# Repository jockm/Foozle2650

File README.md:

# Foozle2650
A Signetics 2650 based SBC based on [Jim11662418's Signetics-2650-SBC](https://github.com/jim11662418/Signetics-2650-SBC)

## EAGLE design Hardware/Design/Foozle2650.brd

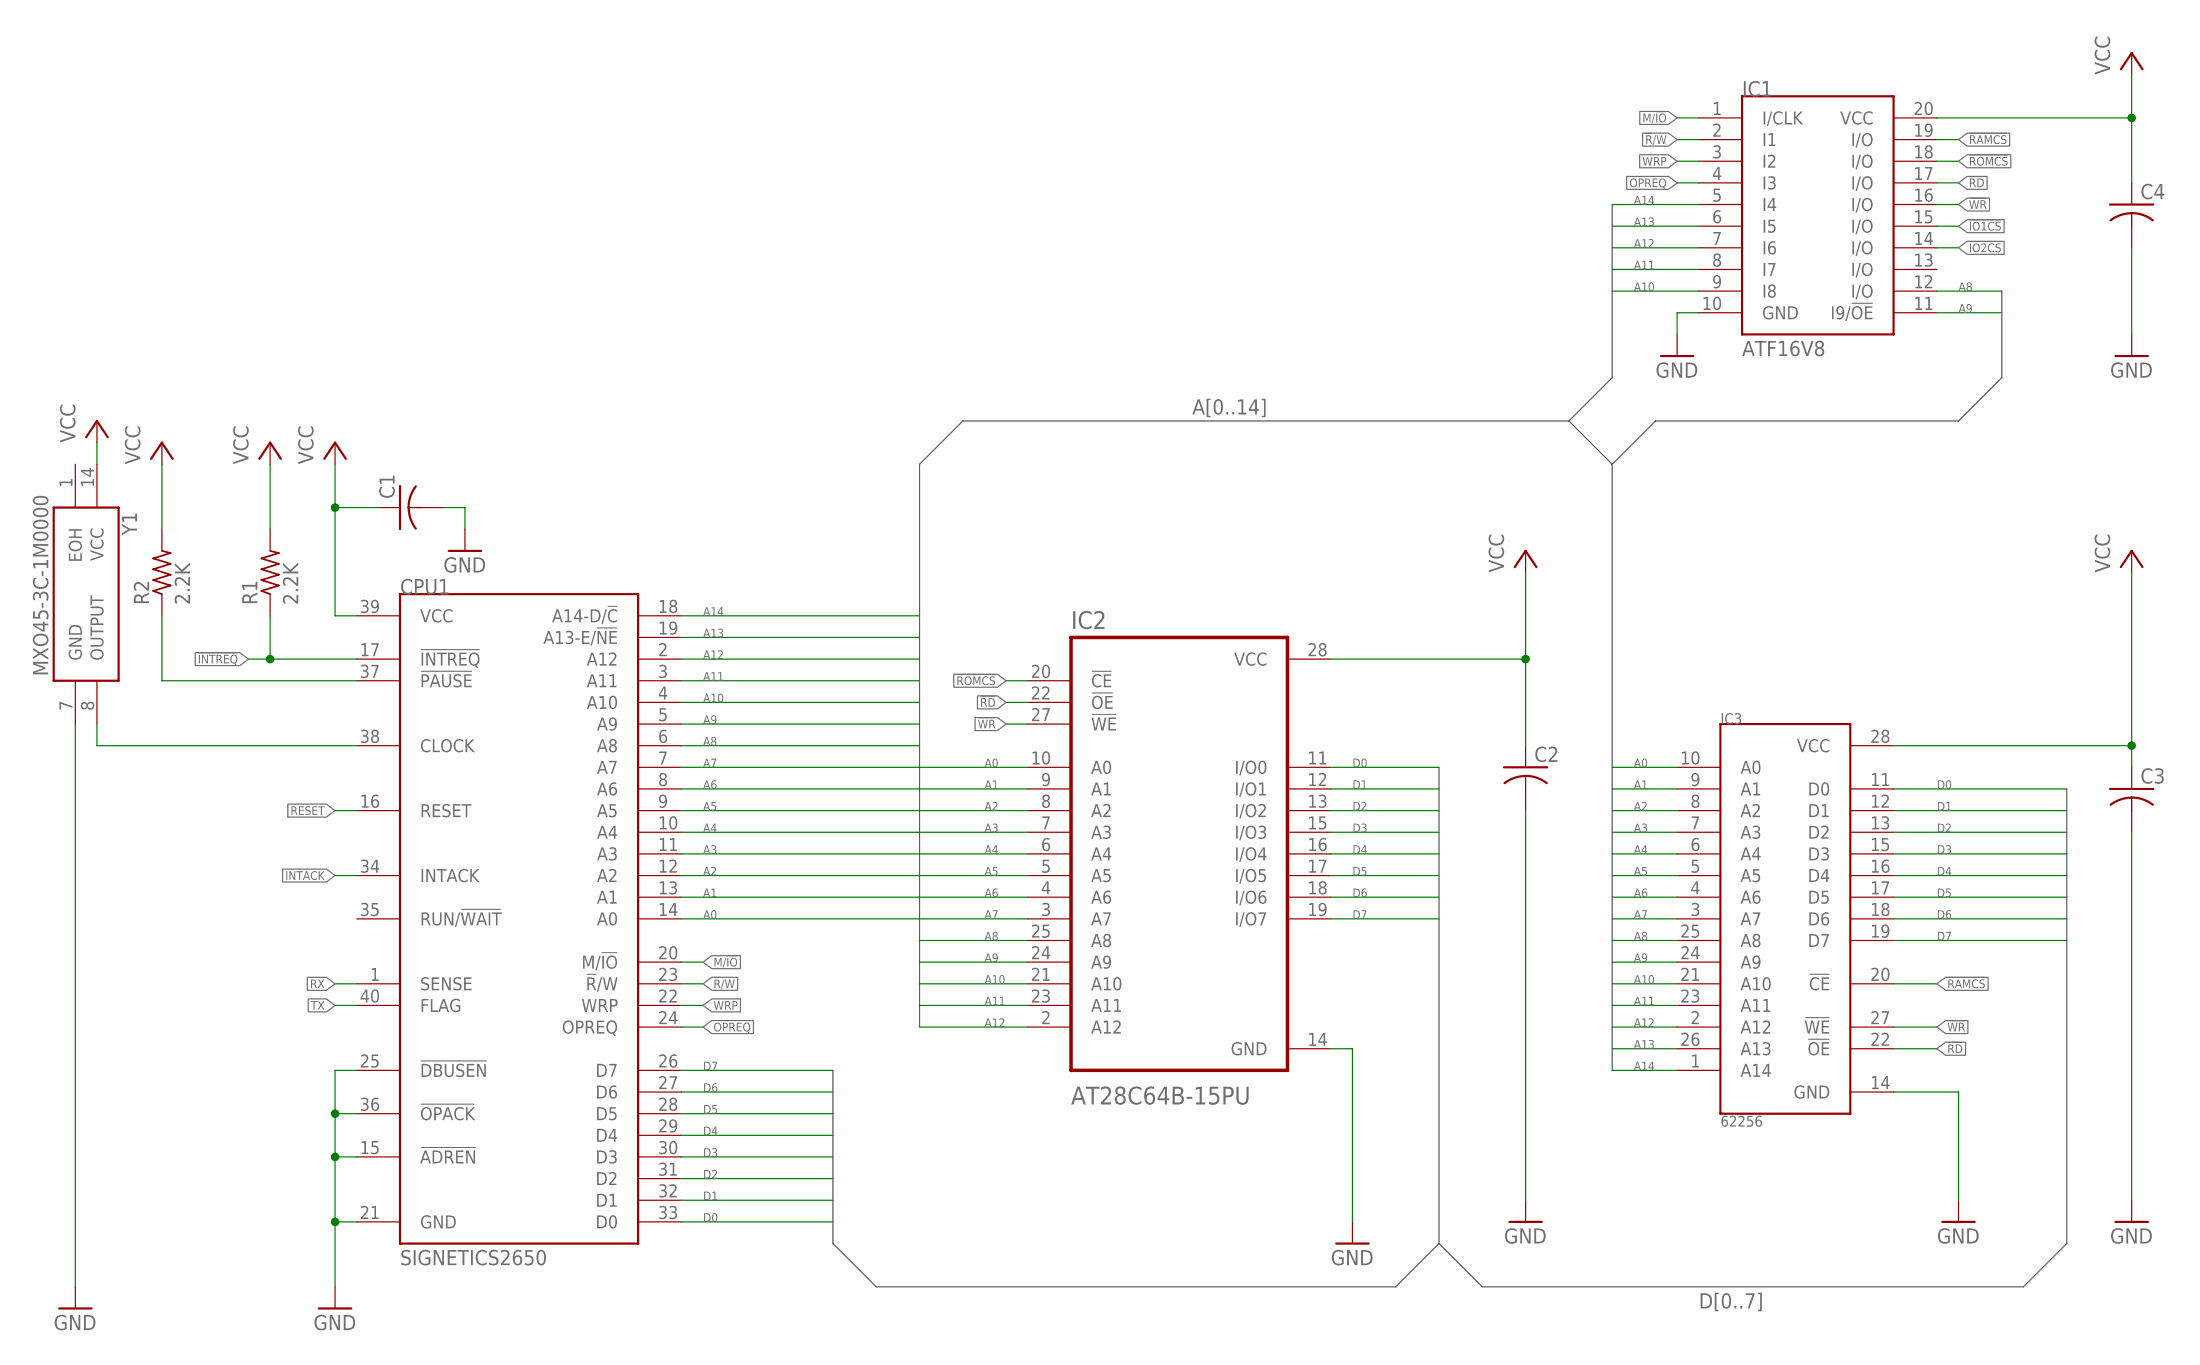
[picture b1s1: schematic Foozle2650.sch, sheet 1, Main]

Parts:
C1, C2, C3, C4: C-US025-024X044; C025-024X044
CPU1: SIGNETICS2650; DIL40
IC1: ATF16V8; DIL20
IC2: AT28C64B-15PU; DIP1555W45P254L3733H482Q28
IC3: 62256; DIP-28/600MIL
R1, R2: 2.2K; 0204/7
Y1: MXO45-3C-1M0000; MXO453C1M0000

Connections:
!INTREQ: CPU1.17 (!INTREQ), R1.1; also elsewhere on the board
!IO1CS: IC1.15 (I/O); also elsewhere on the board
!IO2CS: IC1.14 (I/O); also elsewhere on the board
!R!/W: CPU1.23 (!R!/W), IC1.2 (I1)
!RAMCS: IC1.19 (I/O), IC3.20 (!CE)
!RD: IC1.17 (I/O), IC2.22 (!OE), IC3.22 (!OE); also elsewhere on the board
!ROMCS: IC1.18 (I/O), IC2.20 (!CE)
!WR: IC1.16 (I/O), IC2.27 (!WE), IC3.27 (!WE); also elsewhere on the board
A0: CPU1.14 (A0), IC2.10 (A0), IC3.10 (A0); also elsewhere on the board
A1: CPU1.13 (A1), IC2.9 (A1), IC3.9 (A1); also elsewhere on the board
A2: CPU1.12 (A2), IC2.8 (A2), IC3.8 (A2); also elsewhere on the board
A3: CPU1.11 (A3), IC2.7 (A3), IC3.7 (A3); also elsewhere on the board
A4: CPU1.10 (A4), IC2.6 (A4), IC3.6 (A4); also elsewhere on the board
A5: CPU1.9 (A5), IC2.5 (A5), IC3.5 (A5); also elsewhere on the board
A6: CPU1.8 (A6), IC2.4 (A6), IC3.4 (A6); also elsewhere on the board
A7: CPU1.7 (A7), IC2.3 (A7), IC3.3 (A7)
A8: CPU1.6 (A8), IC1.12 (I/O), IC2.25 (A8), IC3.25 (A8)
A9: CPU1.5 (A9), IC1.11 (I9/!OE), IC2.24 (A9), IC3.24 (A9)
A10: CPU1.4 (A10), IC1.9 (I8), IC2.21 (A10), IC3.21 (A10)
A11: CPU1.3 (A11), IC1.8 (I7), IC2.23 (A11), IC3.23 (A11)
A12: CPU1.2 (A12), IC1.7 (I6), IC2.2 (A12), IC3.2 (A12)
A13: CPU1.19 (A13-E/!NE), IC1.6 (I5), IC3.26 (A13)
A14: CPU1.18 (A14-D/!C), IC1.5 (I4), IC3.1 (A14)
CLOCK: CPU1.38 (CLOCK), Y1.8 (OUTPUT); also elsewhere on the board
D0: CPU1.33 (D0), IC2.11 (I/O0), IC3.11 (D0); also elsewhere on the board
D1: CPU1.32 (D1), IC2.12 (I/O1), IC3.12 (D1); also elsewhere on the board
D2: CPU1.31 (D2), IC2.13 (I/O2), IC3.13 (D2); also elsewhere on the board
D3: CPU1.30 (D3), IC2.15 (I/O3), IC3.15 (D3); also elsewhere on the board
D4: CPU1.29 (D4), IC2.16 (I/O4), IC3.16 (D4); also elsewhere on the board
D5: CPU1.28 (D5), IC2.17 (I/O5), IC3.17 (D5); also elsewhere on the board
D6: CPU1.27 (D6), IC2.18 (I/O6), IC3.18 (D6); also elsewhere on the board
D7: CPU1.26 (D7), IC2.19 (I/O7), IC3.19 (D7); also elsewhere on the board
GND: C1.2, C2.2, C3.2, C4.2, CPU1.15 (!ADREN), CPU1.21 (GND), CPU1.25 (!DBUSEN), CPU1.36 (!OPACK), IC1.10 (GND), IC2.14 (GND), IC3.14 (GND), Y1.7 (GND); also elsewhere on the board
INTACK: CPU1.34 (INTACK); also elsewhere on the board
M/!IO: CPU1.20 (M/!IO), IC1.1 (I/CLK)
unnamed: CPU1.37 (!PAUSE), R2.1
OPREQ: CPU1.24 (OPREQ), IC1.4 (I3)
RESET: CPU1.16 (RESET); also elsewhere on the board
RX: CPU1.1 (SENSE); also elsewhere on the board
TX: CPU1.40 (FLAG); also elsewhere on the board
VCC: C1.1, C2.1, C3.1, C4.1, CPU1.39 (VCC), IC1.20 (VCC), IC2.28 (VCC), IC3.28 (VCC), R1.2, R2.2, Y1.14 (VCC); also elsewhere on the board
WRP: CPU1.22 (WRP), IC1.3 (I2)

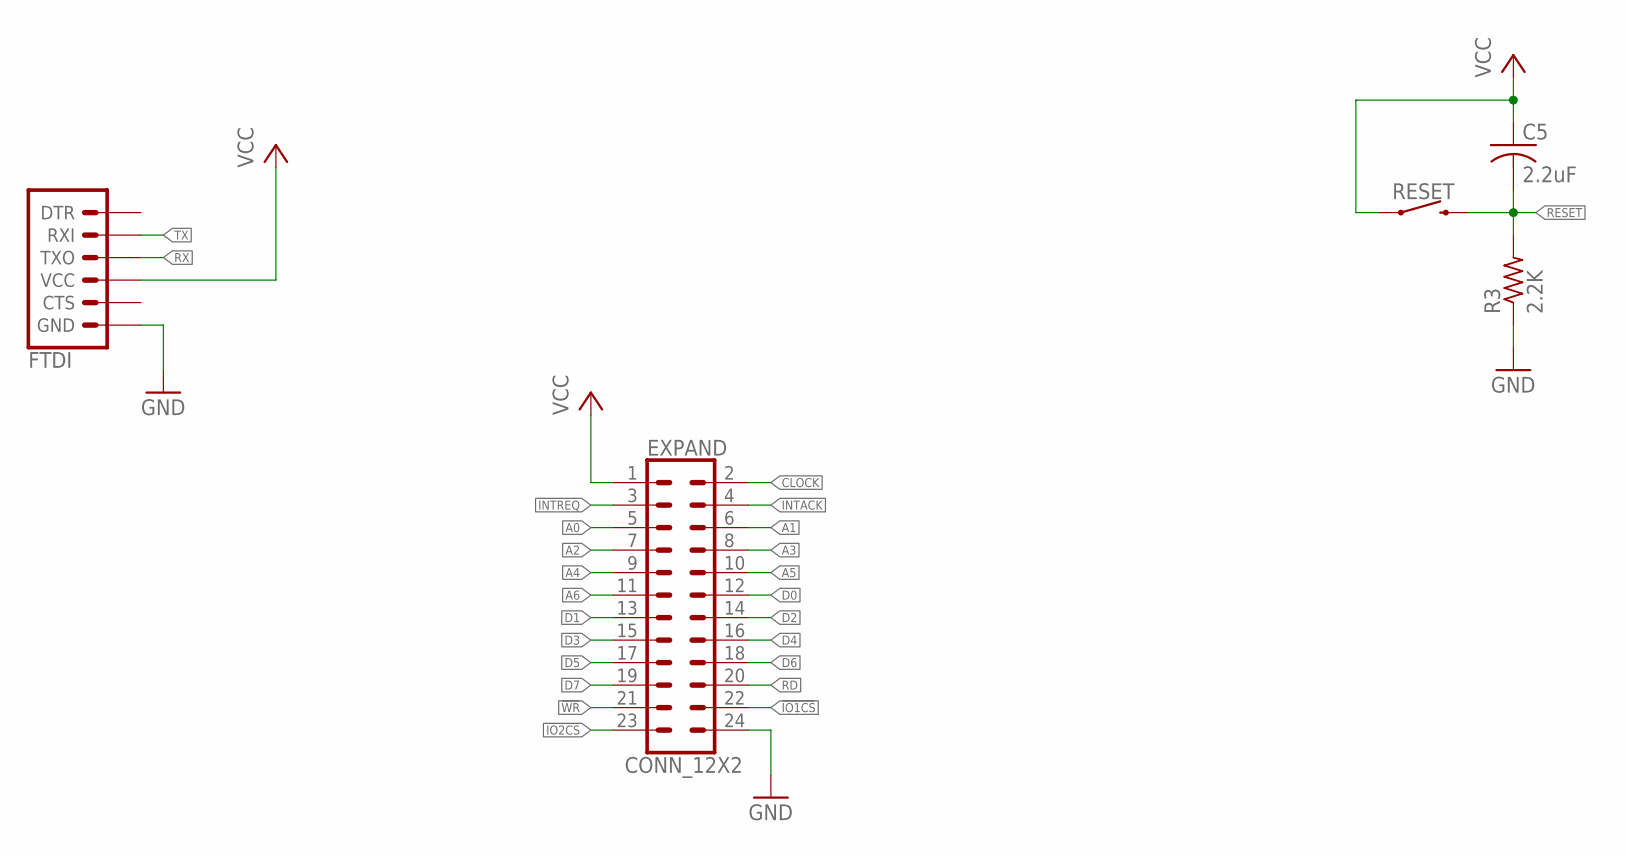
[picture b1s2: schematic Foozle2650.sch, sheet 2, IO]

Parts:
C5: 2.2uF; C025-024X044
EXPAND: CONN_12X2; 2X12
FTDI: 6_PIN_SERIAL_TARGETLONGPADS; 1X06_LONGPADS
R3: 2.2K; 0204/7
RESET: MOMENTARY-SWITCH-SPST-PTH-6.0MM; TACTILE_SWITCH_PTH_6.0MM

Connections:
!INTREQ: EXPAND.3; also elsewhere on the board
!IO1CS: EXPAND.22; also elsewhere on the board
!IO2CS: EXPAND.23; also elsewhere on the board
!RD: EXPAND.20; also elsewhere on the board
!WR: EXPAND.21; also elsewhere on the board
A0: EXPAND.5; also elsewhere on the board
A1: EXPAND.6; also elsewhere on the board
A2: EXPAND.7; also elsewhere on the board
A3: EXPAND.8; also elsewhere on the board
A4: EXPAND.9; also elsewhere on the board
A5: EXPAND.10; also elsewhere on the board
A6: EXPAND.11; also elsewhere on the board
CLOCK: EXPAND.2; also elsewhere on the board
D0: EXPAND.12; also elsewhere on the board
D1: EXPAND.13; also elsewhere on the board
D2: EXPAND.14; also elsewhere on the board
D3: EXPAND.15; also elsewhere on the board
D4: EXPAND.16; also elsewhere on the board
D5: EXPAND.17; also elsewhere on the board
D6: EXPAND.18; also elsewhere on the board
D7: EXPAND.19; also elsewhere on the board
GND: EXPAND.24, FTDI.6 (GND), R3.1; also elsewhere on the board
INTACK: EXPAND.4; also elsewhere on the board
RESET: C5.2, R3.2, RESET.3 (2); also elsewhere on the board
RX: FTDI.3 (TXO); also elsewhere on the board
TX: FTDI.2 (RXI); also elsewhere on the board
VCC: C5.1, EXPAND.1, FTDI.4 (VCC), RESET.1; also elsewhere on the board

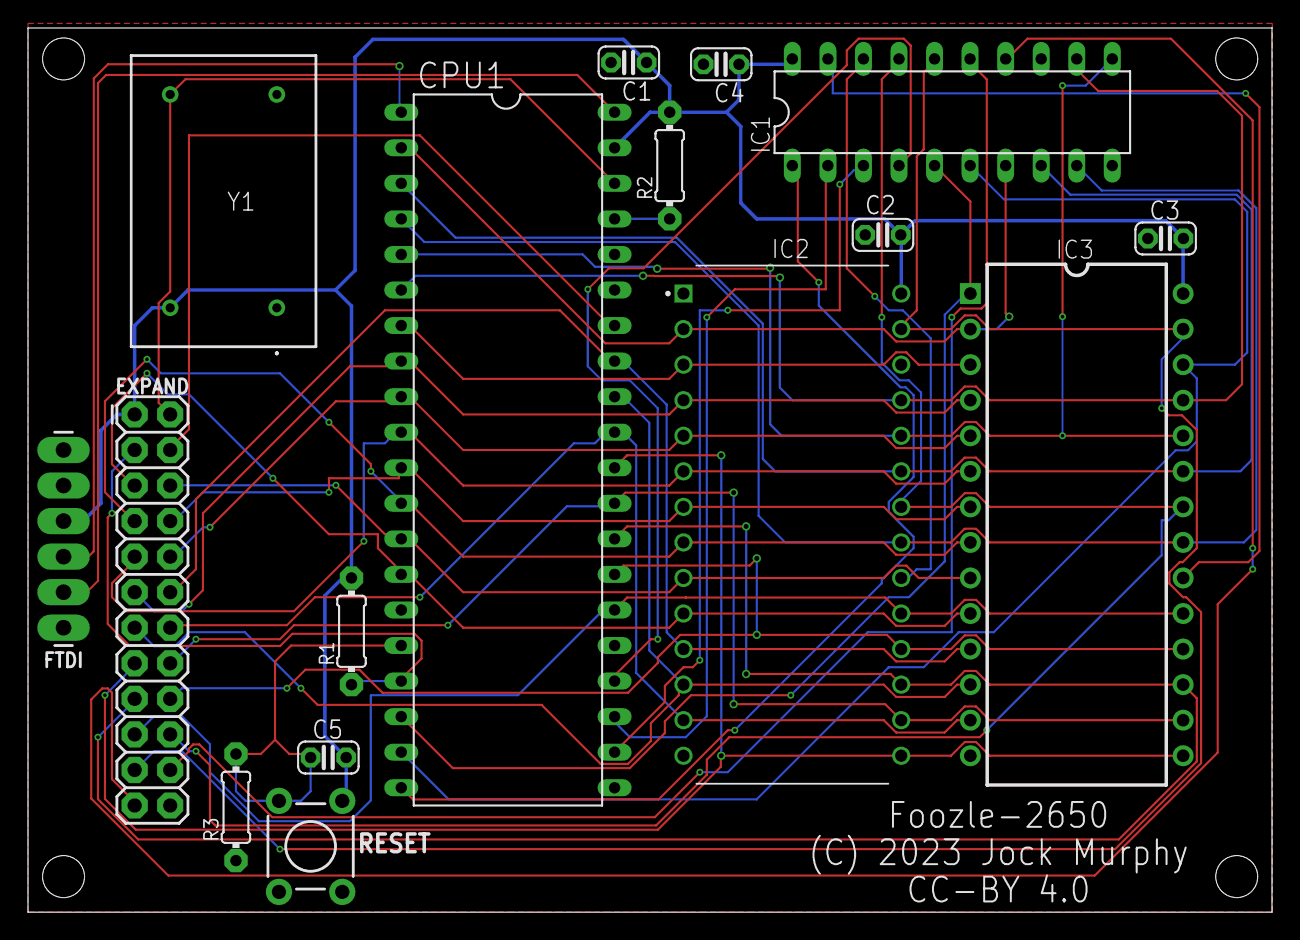
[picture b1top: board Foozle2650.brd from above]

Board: 2 copper layers, 88.9 x 63.2 mm, 16 parts (0 on the bottom side), 42 nets.

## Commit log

2023-09-27 Inistial Checkin
2023-09-27 Update README.md
    Added link to inspiring project
2023-09-27 Added firmware
2023-09-27 Added assembled firmware
2023-09-27 Connected A9 to PLD

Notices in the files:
Hardware/Design/Foozle2650.brd:
(C) 2023 Jock Murphy
CC-BY 4.0
parts and their libraries:
SparkFun-Connectors: Licensing: Creative Commons ShareAlike 4.0 International - https://creativecommons.org/licenses/by-sa/4.0
